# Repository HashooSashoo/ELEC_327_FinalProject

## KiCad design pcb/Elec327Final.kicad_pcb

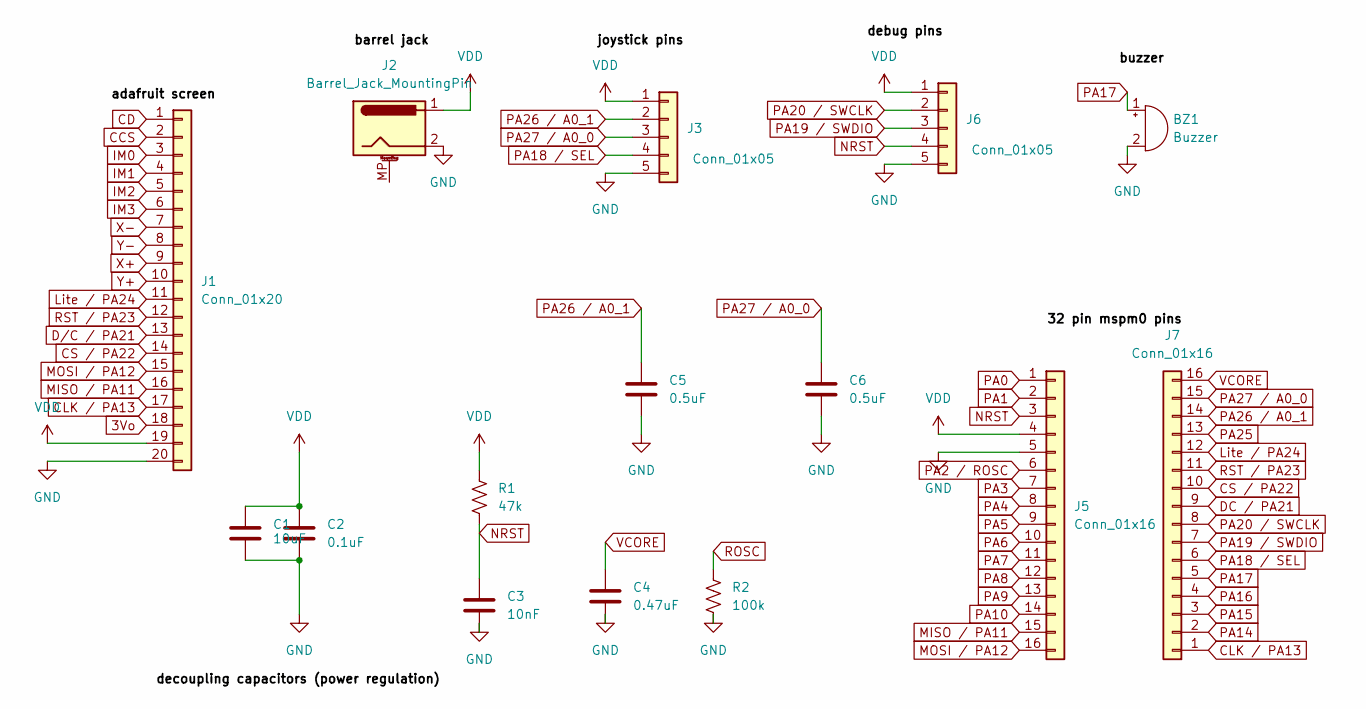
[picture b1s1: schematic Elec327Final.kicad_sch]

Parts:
BZ1: Buzzer; Buzzer_Murata_PKLCS1212E
C1: 10uF; C_1206_3216Metric_Pad1.33x1.80mm_HandSolder
C2: 0.1uF; C_1206_3216Metric_Pad1.33x1.80mm_HandSolder
C3: 10nF; C_1206_3216Metric_Pad1.33x1.80mm_HandSolder
C4: 0.47uF; C_1206_3216Metric_Pad1.33x1.80mm_HandSolder
C5, C6: 0.5uF; C_1206_3216Metric_Pad1.33x1.80mm_HandSolder
J1: Conn_01x20; PinHeader_1x20_P2.54mm_Vertical
J2: Barrel_Jack_MountingPin; BarrelJack_CUI_PJ-063AH_Horizontal
J3, J6: Conn_01x05; PinHeader_1x05_P2.54mm_Vertical
J5, J7: Conn_01x16; PinHeader_1x16_P2.54mm_Vertical
R1: 47k; R_1206_3216Metric_Pad1.30x1.75mm_HandSolder
R2: 100k; R_1206_3216Metric_Pad1.30x1.75mm_HandSolder

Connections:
3Vo: J1.18
CCS: J1.2
CD: J1.1
CLK / PA13: J1.17, J7.1
CS / PA22: J1.14, J7.10
DC / PA21: J7.9
D/C / PA21: J1.13
GND: BZ1.2 (-), C1.2, C2.2, C3.2, C4.2, C5.2, C6.2, J1.20, J2.2, J3.5, J5.5, J6.5, R2.2
IM0: J1.3
IM1: J1.4
IM2: J1.5
IM3: J1.6
Lite / PA24: J1.11, J7.12
MISO / PA11: J1.16, J5.15
MOSI / PA12: J1.15, J5.16
NRST: C3.1, J5.3, J6.4, R1.2
PA0: J5.1
PA1: J5.2
PA2 / ROSC: J5.6
PA3: J5.7
PA4: J5.8
PA5: J5.9
PA6: J5.10
PA7: J5.11
PA8: J5.12
PA9: J5.13
PA10: J5.14
PA14: J7.2
PA15: J7.3
PA16: J7.4
PA17: BZ1.1 (+), J7.5
PA18 / SEL: J3.4, J7.6
PA19 / SWDIO: J6.3, J7.7
PA20 / SWCLK: J6.2, J7.8
PA25: J7.13
PA26 / A0_1: C5.1, J3.2, J7.14
PA27 / A0_0: C6.1, J3.3, J7.15
ROSC: R2.1
RST / PA23: J1.12, J7.11
VCORE: C4.1, J7.16
VDD: C1.1, C2.1, J1.19, J2.1, J3.1, J5.4, J6.1, R1.1
X+: J1.9
X-: J1.7
Y+: J1.10
Y-: J1.8

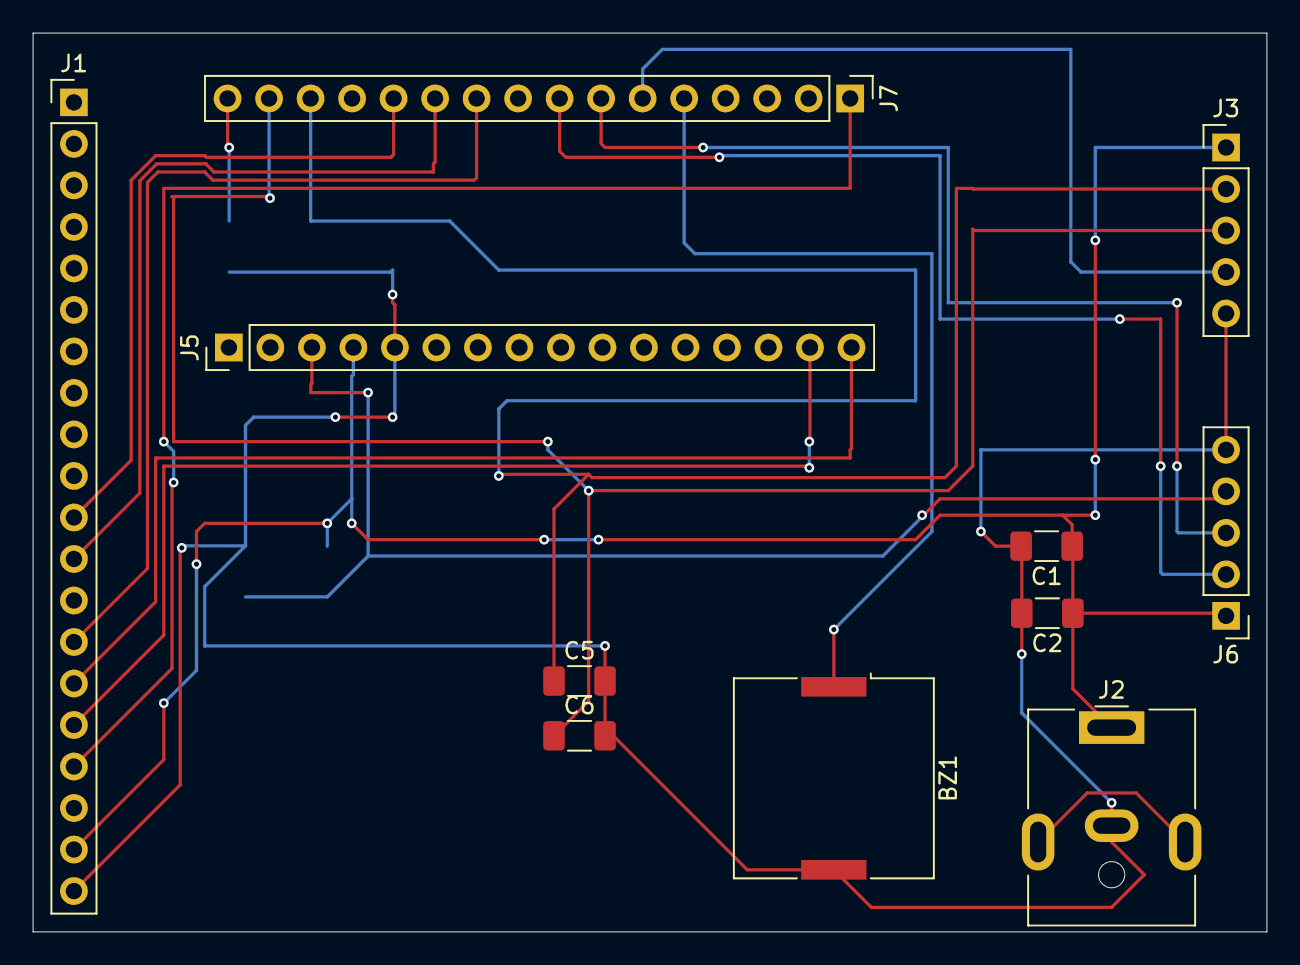
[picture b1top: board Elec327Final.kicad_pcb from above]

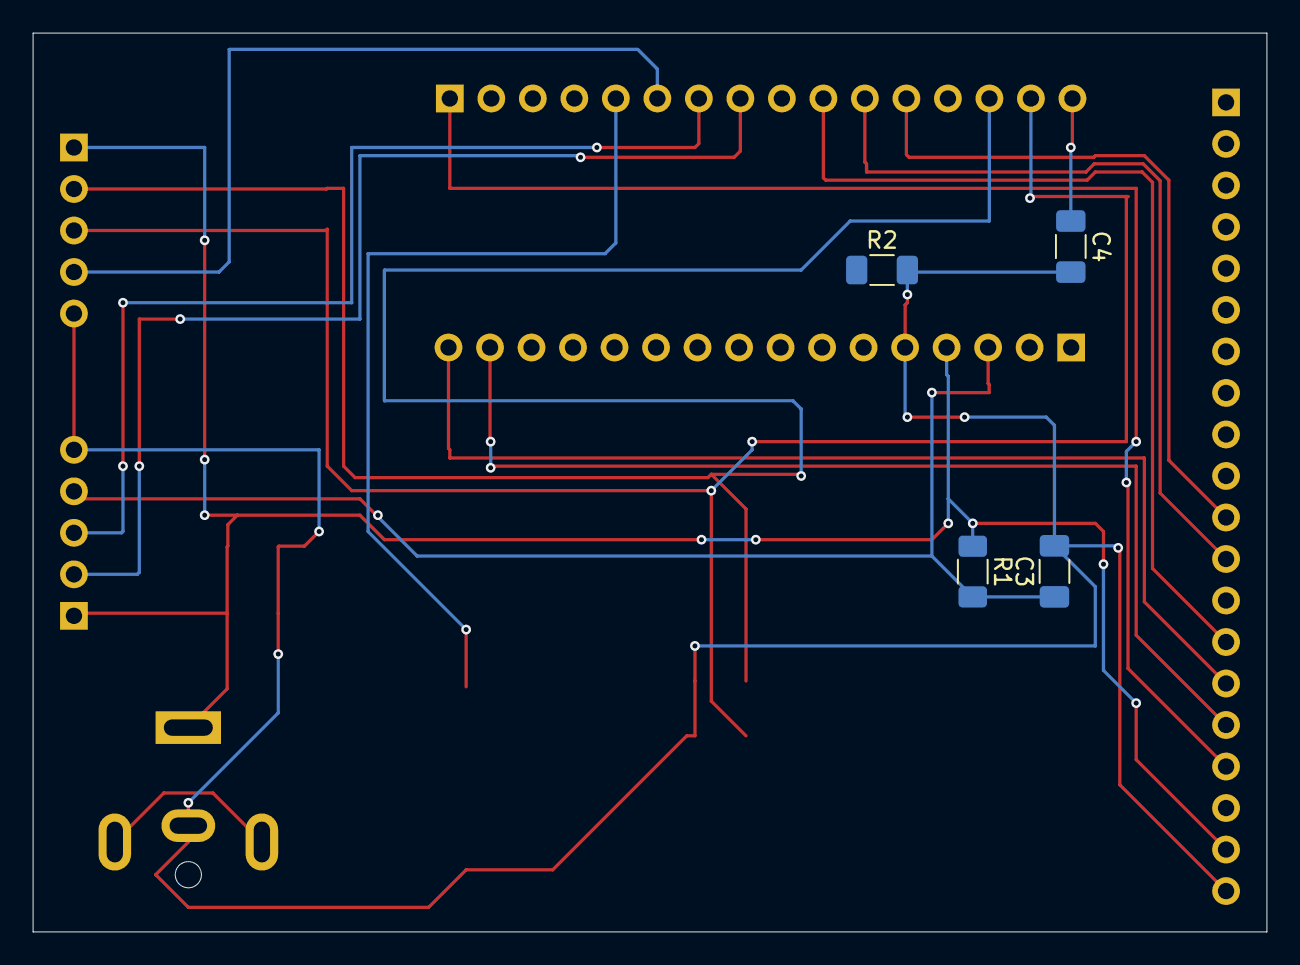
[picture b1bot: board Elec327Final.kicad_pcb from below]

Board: 2 copper layers, 75.5 x 55.0 mm, 15 parts (4 on the bottom side), 16 nets.

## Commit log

2026-04-20 initial commit, contains SPI and GPIO initialization code, commands for LCD screen, and a function to maek background color
2026-04-21 feat: peripheral init (ADC,TIMG2,TIMA0,NVM)
2026-04-23 added functions to get horizontal, vertical ADC values
2026-04-23 added get horizontal, vertical declarations
2026-04-23 fixed typos
2026-04-24 finalized pin assignments for buzzer and button
2026-05-10 Add files via upload
    uploaded all screen code
2026-05-14 first fully functioning game file uploads
2026-05-14 Delete peripherals.h
    not needed
2026-05-14 Delete peripherals.c
    not needed
2026-05-16 LOTS of changes, reorganized files, added initial draft of website, pcb files, col pictures, etc.
2026-05-16 renamed website to docs for github pages hosting
2026-05-16 Create CNAME
2026-05-16 added cubes to website, changes format and added things
2026-05-16 more changes and a huge change in website
2026-05-16 added presentation video
2026-05-17 added the demo video
2026-05-17 added descriptions to gallery
2026-05-17 final edits
